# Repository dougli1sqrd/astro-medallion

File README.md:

# Astro Medallion

Electronics schematics, PCB layout, and software for the Astro Medallion.

The Astro Medallion is a 12 sided circuit board with LEDs that represent the astrological planets and their positions as a sort of clock. Earth is in the middle of 12 spokes of addressable RGB LEDs, where each spoke represents a sky position in the elliptical - each 30 degree section one of the zodiac signs. The distance along each spoke represents the distance away from the each planet is from the earth. Since it's geocentric planets may sometimes be closer or farther away from each other. Each planet will have a unique color.

There are Warm White LEDs along the edge of the PCB which represents the current field of view from your position on Earth - which rotates around the board once every 24 hours.

The project is a kind of translation of this page: https://ericofftherails.city/astrosim/

The LEDs are controlled by an esp32c3 microcontroller on a development board.

# Software

Fundamentally, the software controlling the board needs to:
1. Read the time in the RTC (Real Time Clock) chip on the PCB
2. Calculate Planetary positions
   1. Compute the positions of the planets relative to the earth based on the current time
   2. Compute the "facing" horizon position
3. Update the Display
   1. Send color data to the Addressable LEDs representing where each Planet is with respect to the zodiac sign
   2. Send white LED data representing the current horizon position
4. Sleep, and then awaken in time for the next update

Additionally, the software will have to be configurable mainly in setting the current time. Reading and Writing the current time will go over I2C to the RTC chip on board. This perhaps could be accomplished with a basic serial command line

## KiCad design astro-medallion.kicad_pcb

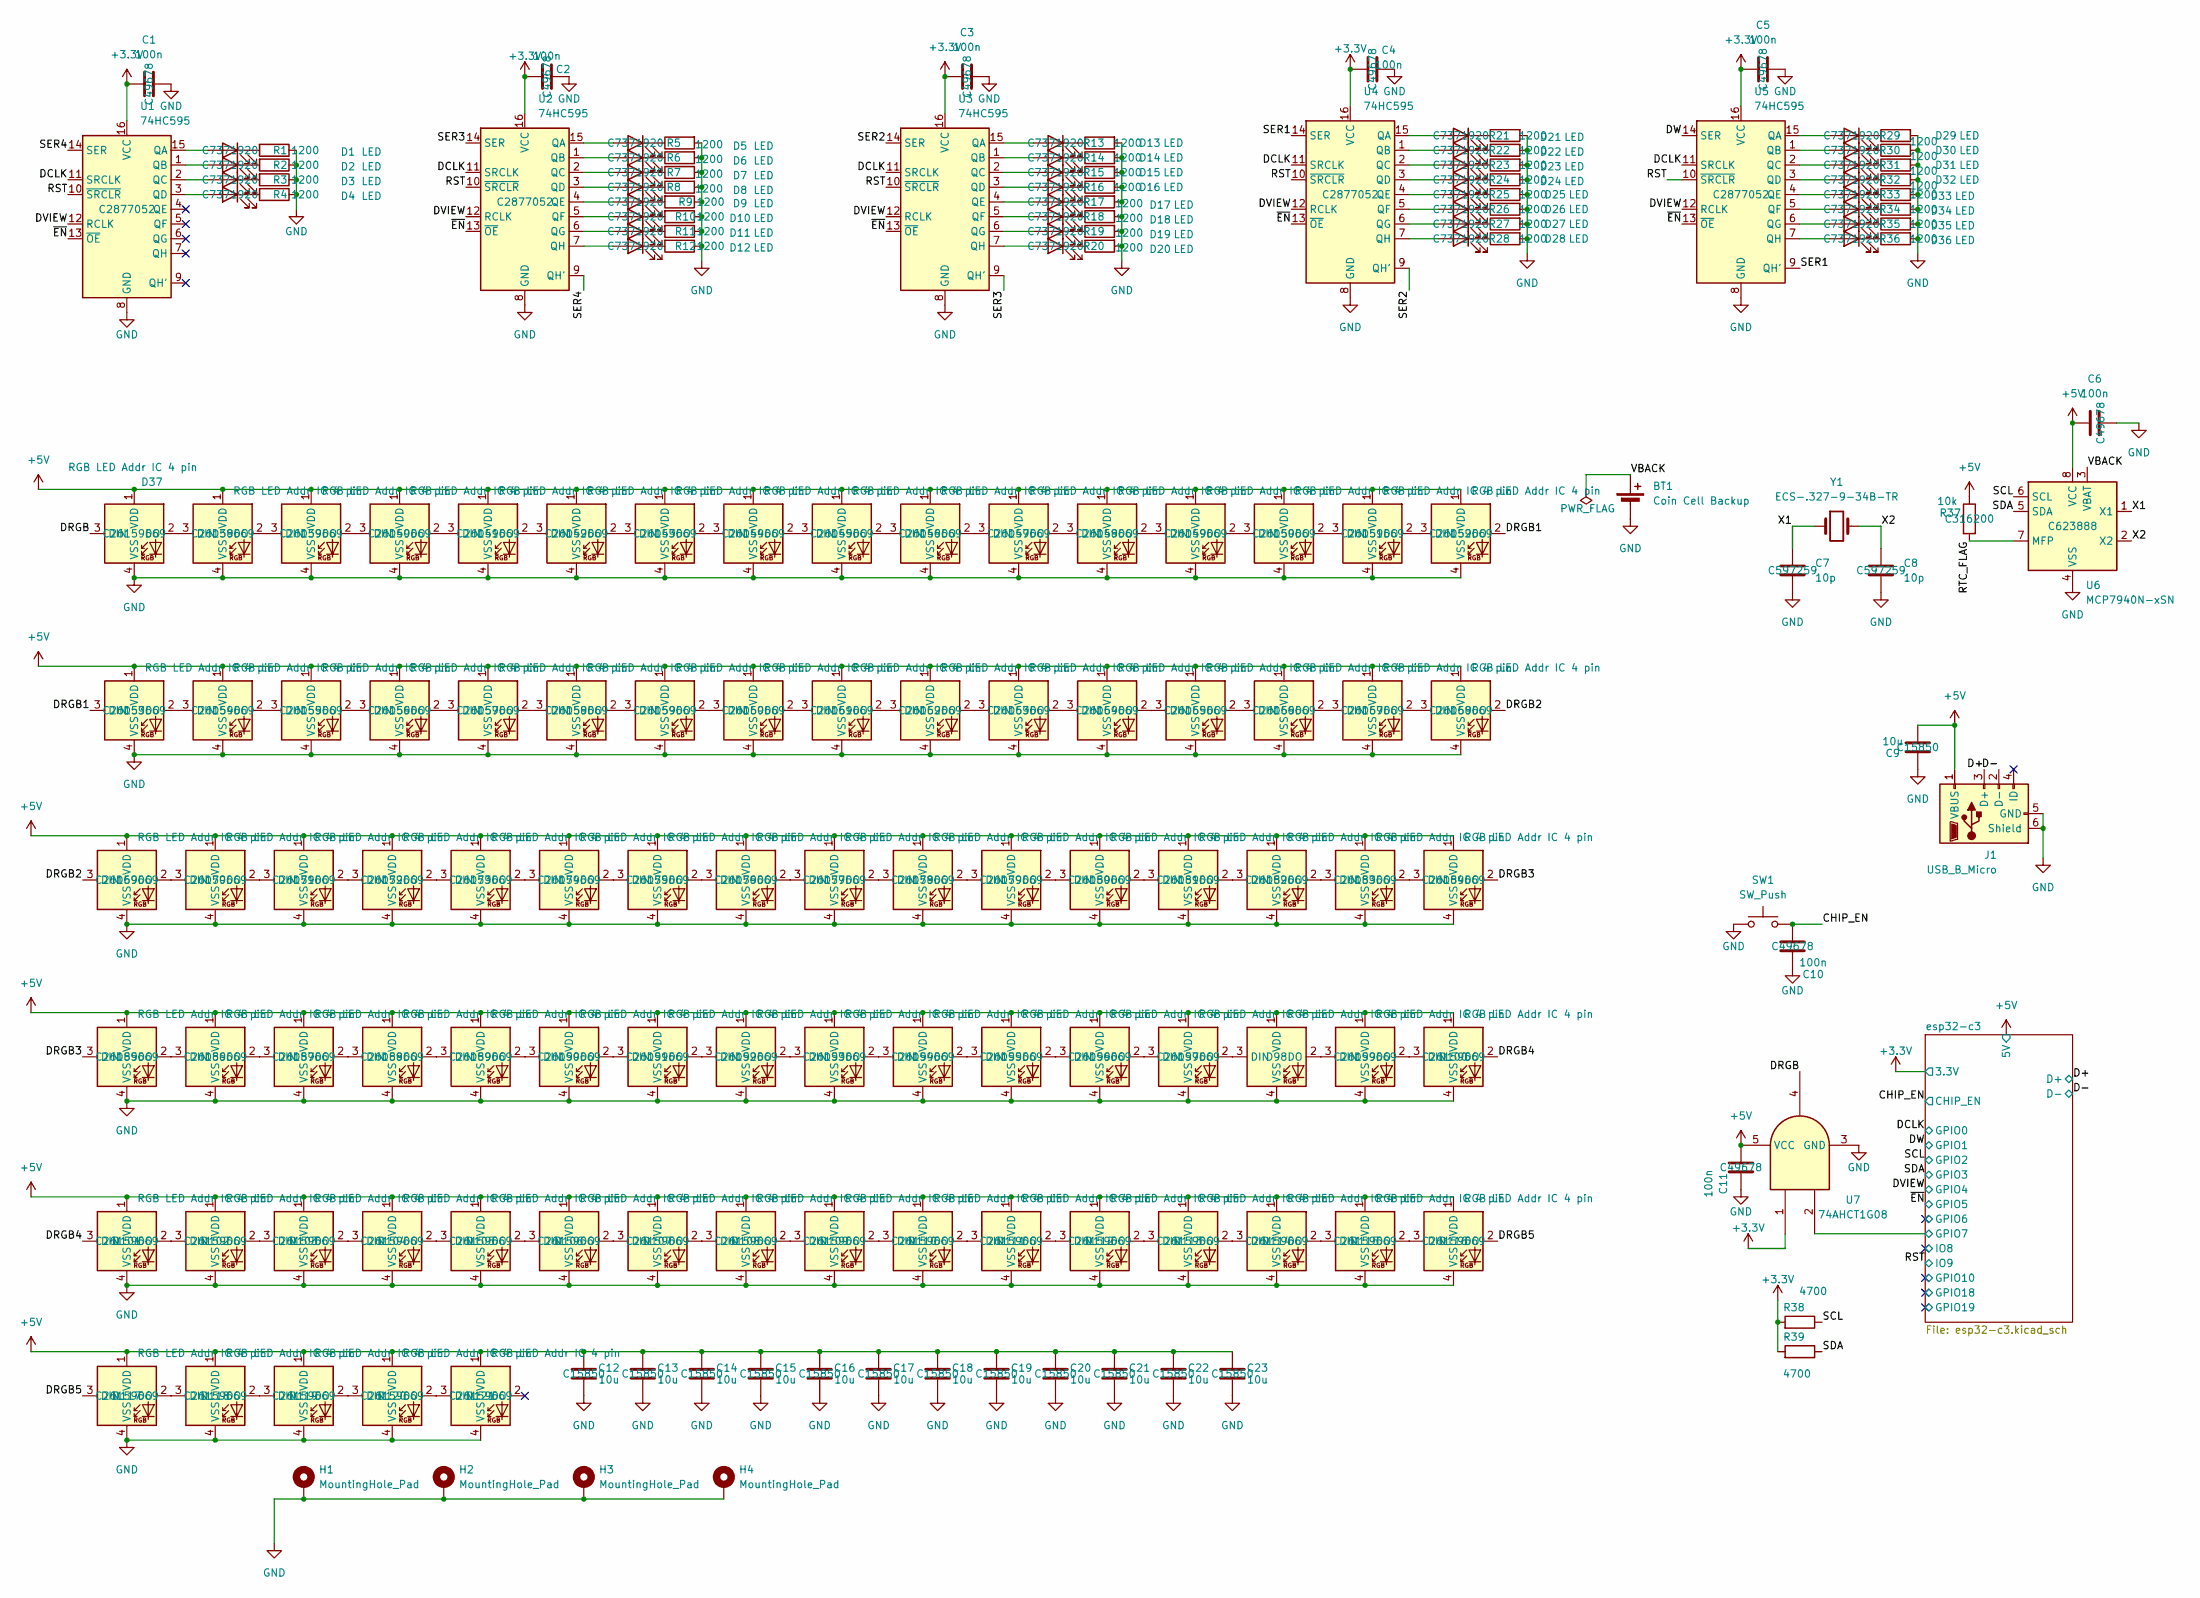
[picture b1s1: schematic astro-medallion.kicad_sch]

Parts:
BT1: Coin Cell Backup; BatteryHolder_Keystone_3002_1x2032
C1, C2, C3, C4, C5, C6, C10, C11: 100n; C_0805_2012Metric_Pad1.18x1.45mm_HandSolder; LCSC C49678
C7, C8: 10p; C_0805_2012Metric_Pad1.18x1.45mm_HandSolder; LCSC C597259
C9, C12, C13, C14, C15, C16, C17, C18, C19, C20, C21, C22, C23: 10u; C_0805_2012Metric_Pad1.18x1.45mm_HandSolder; LCSC C15850
D1, D2, D3, D4, D5, D6, D7, D8, D9, D10, D11, D12, D13, D14, D15, D16, D17, D18, D19, D20, D21, D22, D23, D24, D25, D26, D27, D28, D29, D30, D31, D32, D33, D34, D35, D36: LED; LED_PLCC_2835_Handsoldering; LCSC C7371920
D37, D38, D39, D40, D41, D42, D43, D44, D45, D46, D47, D48, D49, D50, D51, D52, D53, D54, D55, D56, D57, D58, D59, D60, D61, D62, D63, D64, D65, D66, D67, D68, D69, D70, D71, D72, D73, D74, D75, D76, D77, D78, D79, D80, D81, D82, D83, D84, D85, D86, D87, D88, D89, D90, D91, D92, D93, D94, D95, D96, D97, D98, D99, D100, D101, D102, D103, D104, D105, D106, D107, D108, D109, D110, D111, D112, D113, D114, D115, D116, D117, D118, D119, D120, D121: RGB LED Addr IC 4 pin; LED_PLCC3528_4P; LCSC C26159669
H1, H2, H3, H4: MountingHole_Pad; MountingHole_3.2mm_M3_Pad
J1: USB_B_Micro; USB_Micro-B_Molex-105133-0001; LCSC C586226
R1, R2, R3, R4, R5, R6, R7, R8, R9, R10, R11, R12, R13, R14, R15, R16, R17, R18, R19, R20, R21, R22, R23, R24, R25, R26, R27, R28, R29, R30, R31, R32, R33, R34, R35, R36: 1200; R_0805_2012Metric_Pad1.20x1.40mm_HandSolder
R37: 10k; R_0805_2012Metric_Pad1.20x1.40mm_HandSolder; LCSC C316200
R38, R39: 4700; R_0805_2012Metric_Pad1.20x1.40mm_HandSolder
SW1: SW_Push; SW_SPST_PTS645
U1, U2, U3, U4, U5: 74HC595; TSSOP-16_4.4x5mm_P0.65mm; LCSC C2877052
U6: MCP7940N-xSN; SOIC-8_3.9x4.9mm_P1.27mm; LCSC C623888
U7: 74AHCT1G08; SOT-23-5_HandSoldering; LCSC C460499
Y1: ECS-.327-9-34B-TR; Crystal_SMD_3215-2Pin_3.2x1.5mm; LCSC C2848222

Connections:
+3.3V: C1.1, C2.1, C3.1, C4.1, C5.1, R38.2, R39.2, U1.16 (VCC), U2.16 (VCC), U3.16 (VCC), U4.16 (VCC), U5.16 (VCC), U7.1; also elsewhere on the board
+5V: C6.1, C9.1, C11.1, C12.2, C13.2, C14.2, C15.2, C16.2, C17.2, C18.2, C19.2, C20.2, C21.2, C22.2, C23.2, D37.1 (VDD), D38.1 (VDD), D39.1 (VDD), D40.1 (VDD), D41.1 (VDD), D42.1 (VDD), D43.1 (VDD), D44.1 (VDD), D45.1 (VDD), D46.1 (VDD), D47.1 (VDD), D48.1 (VDD), D49.1 (VDD), D50.1 (VDD), D51.1 (VDD), D52.1 (VDD), D53.1 (VDD), D54.1 (VDD), D55.1 (VDD), D56.1 (VDD), D57.1 (VDD), D58.1 (VDD), D59.1 (VDD), D60.1 (VDD), D61.1 (VDD), D62.1 (VDD), D63.1 (VDD), D64.1 (VDD), D65.1 (VDD), D66.1 (VDD), D67.1 (VDD), D68.1 (VDD), D69.1 (VDD), D70.1 (VDD), D71.1 (VDD), D72.1 (VDD), D73.1 (VDD), D74.1 (VDD), D75.1 (VDD), D76.1 (VDD), D77.1 (VDD), D78.1 (VDD), D79.1 (VDD), D80.1 (VDD), D81.1 (VDD), D82.1 (VDD), D83.1 (VDD), D84.1 (VDD), D85.1 (VDD), D86.1 (VDD), D87.1 (VDD), D88.1 (VDD), D89.1 (VDD), D90.1 (VDD), D91.1 (VDD), D92.1 (VDD), D93.1 (VDD), D94.1 (VDD), D95.1 (VDD), D96.1 (VDD), D97.1 (VDD), D98.1 (VDD), D99.1 (VDD), D100.1 (VDD), D101.1 (VDD), D102.1 (VDD), D103.1 (VDD), D104.1 (VDD), D105.1 (VDD), D106.1 (VDD), D107.1 (VDD), D108.1 (VDD), D109.1 (VDD), D110.1 (VDD), D111.1 (VDD), D112.1 (VDD), D113.1 (VDD), D114.1 (VDD), D115.1 (VDD), D116.1 (VDD), D117.1 (VDD), D118.1 (VDD), D119.1 (VDD), D120.1 (VDD), D121.1 (VDD), J1.1 (VBUS), R37.1, U6.8 (VCC), U7.5 (VCC); also elsewhere on the board
/CHIP_EN: C10.2, SW1.2; also elsewhere on the board
/D+: J1.3 (D+); also elsewhere on the board
/D-: J1.2 (D-); also elsewhere on the board
/DCLK: U1.11 (SRCLK), U2.11 (SRCLK), U3.11 (SRCLK), U4.11 (SRCLK), U5.11 (SRCLK); also elsewhere on the board
/DRGB: D37.3 (DIN), U7.4
/DRGB1: D52.2 (DO), D53.3 (DIN)
/DRGB2: D68.2 (DO), D69.3 (DIN)
/DRGB3: D84.2 (DO), D85.3 (DIN)
/DRGB4: D100.2 (DO), D101.3 (DIN)
/DRGB5: D116.2 (DO), D117.3 (DIN)
/DVIEW: U1.12 (RCLK), U2.12 (RCLK), U3.12 (RCLK), U4.12 (RCLK), U5.12 (RCLK); also elsewhere on the board
/DW: U5.14 (SER); also elsewhere on the board
/RST: U1.10 (~SRCLR), U2.10 (~SRCLR), U3.10 (~SRCLR), U4.10 (~SRCLR), U5.10 (~SRCLR); also elsewhere on the board
/RTC_FLAG: R37.2, U6.7 (MFP)
/SCL: R38.1, U6.6 (SCL); also elsewhere on the board
/SDA: R39.1, U6.5 (SDA); also elsewhere on the board
/SER1: U4.14 (SER), U5.9 (QH')
/SER2: U3.14 (SER), U4.9 (QH')
/SER3: U2.14 (SER), U3.9 (QH')
/SER4: U1.14 (SER), U2.9 (QH')
/VBACK: BT1.1 (+), U6.3 (VBAT)
/X1: C7.1, U6.1 (X1), Y1.1
/X2: C8.1, U6.2 (X2), Y1.2
/esp32-c3/GPIO7: U7.2; also elsewhere on the board
/~EN: U1.13 (~OE), U2.13 (~OE), U3.13 (~OE), U4.13 (~OE), U5.13 (~OE); also elsewhere on the board
GND: BT1.2 (-), C1.2, C2.2, C3.2, C4.2, C5.2, C6.2, C7.2, C8.2, C9.2, C10.1, C11.2, C12.1, C13.1, C14.1, C15.1, C16.1, C17.1, C18.1, C19.1, C20.1, C21.1, C22.1, C23.1, D37.4 (VSS), D38.4 (VSS), D39.4 (VSS), D40.4 (VSS), D41.4 (VSS), D42.4 (VSS), D43.4 (VSS), D44.4 (VSS), D45.4 (VSS), D46.4 (VSS), D47.4 (VSS), D48.4 (VSS), D49.4 (VSS), D50.4 (VSS), D51.4 (VSS), D52.4 (VSS), D53.4 (VSS), D54.4 (VSS), D55.4 (VSS), D56.4 (VSS), D57.4 (VSS), D58.4 (VSS), D59.4 (VSS), D60.4 (VSS), D61.4 (VSS), D62.4 (VSS), D63.4 (VSS), D64.4 (VSS), D65.4 (VSS), D66.4 (VSS), D67.4 (VSS), D68.4 (VSS), D69.4 (VSS), D70.4 (VSS), D71.4 (VSS), D72.4 (VSS), D73.4 (VSS), D74.4 (VSS), D75.4 (VSS), D76.4 (VSS), D77.4 (VSS), D78.4 (VSS), D79.4 (VSS), D80.4 (VSS), D81.4 (VSS), D82.4 (VSS), D83.4 (VSS), D84.4 (VSS), D85.4 (VSS), D86.4 (VSS), D87.4 (VSS), D88.4 (VSS), D89.4 (VSS), D90.4 (VSS), D91.4 (VSS), D92.4 (VSS), D93.4 (VSS), D94.4 (VSS), D95.4 (VSS), D96.4 (VSS), D97.4 (VSS), D98.4 (VSS), D99.4 (VSS), D100.4 (VSS), D101.4 (VSS), D102.4 (VSS), D103.4 (VSS), D104.4 (VSS), D105.4 (VSS), D106.4 (VSS), D107.4 (VSS), D108.4 (VSS), D109.4 (VSS), D110.4 (VSS), D111.4 (VSS), D112.4 (VSS), D113.4 (VSS), D114.4 (VSS), D115.4 (VSS), D116.4 (VSS), D117.4 (VSS), D118.4 (VSS), D119.4 (VSS), D120.4 (VSS), D121.4 (VSS), H1.1, H2.1, H3.1, H4.1, J1.5 (GND), J1.6 (Shield), R1.1, R2.1, R3.1, R4.1, R5.2, R6.2, R7.2, R8.2, R9.1, R10.1, R11.1, R12.1, R13.2, R14.2, R15.2, R16.2, R17.2, R18.2, R19.2, R20.2, R21.2, R22.2, R23.2, R24.2, R25.2, R26.2, R27.2, R28.2, R29.2, R30.2, R31.2, R32.2, R33.2, R34.2, R35.2, R36.2, SW1.1, U1.8 (GND), U2.8 (GND), U3.8 (GND), U4.8 (GND), U5.8 (GND), U6.4 (VSS), U7.3 (GND); also elsewhere on the board
unnamed: D1.2 (A), U1.15 (QA)
unnamed: D1.1 (K), R1.2
unnamed: D2.2 (A), U1.1 (QB)
unnamed: D2.1 (K), R2.2
unnamed: D3.2 (A), U1.2 (QC)
unnamed: D3.1 (K), R3.2
unnamed: D4.2 (A), U1.3 (QD)
unnamed: D4.1 (K), R4.2
unnamed: D5.2 (A), U2.15 (QA)
unnamed: D5.1 (K), R5.1
unnamed: D6.2 (A), U2.1 (QB)
unnamed: D6.1 (K), R6.1
unnamed: D7.2 (A), U2.2 (QC)
unnamed: D7.1 (K), R7.1
unnamed: D8.2 (A), U2.3 (QD)
unnamed: D8.1 (K), R8.1
unnamed: D9.2 (A), U2.4 (QE)
unnamed: D9.1 (K), R9.2
unnamed: D10.2 (A), U2.5 (QF)
unnamed: D10.1 (K), R10.2
unnamed: D11.2 (A), U2.6 (QG)
unnamed: D11.1 (K), R11.2
unnamed: D12.2 (A), U2.7 (QH)
unnamed: D12.1 (K), R12.2
unnamed: D13.2 (A), U3.15 (QA)
unnamed: D13.1 (K), R13.1
unnamed: D14.2 (A), U3.1 (QB)
unnamed: D14.1 (K), R14.1
unnamed: D15.2 (A), U3.2 (QC)
unnamed: D15.1 (K), R15.1
unnamed: D16.2 (A), U3.3 (QD)
unnamed: D16.1 (K), R16.1
unnamed: D17.2 (A), U3.4 (QE)
unnamed: D17.1 (K), R17.1
unnamed: D18.2 (A), U3.5 (QF)
unnamed: D18.1 (K), R18.1
unnamed: D19.2 (A), U3.6 (QG)
unnamed: D19.1 (K), R19.1
unnamed: D20.2 (A), U3.7 (QH)
unnamed: D20.1 (K), R20.1
unnamed: D21.2 (A), U4.15 (QA)
unnamed: D21.1 (K), R21.1
unnamed: D22.2 (A), U4.1 (QB)
unnamed: D22.1 (K), R22.1
unnamed: D23.2 (A), U4.2 (QC)
unnamed: D23.1 (K), R23.1
unnamed: D24.2 (A), U4.3 (QD)
unnamed: D24.1 (K), R24.1
unnamed: D25.2 (A), U4.4 (QE)
unnamed: D25.1 (K), R25.1
unnamed: D26.2 (A), U4.5 (QF)
unnamed: D26.1 (K), R26.1
unnamed: D27.2 (A), U4.6 (QG)
unnamed: D27.1 (K), R27.1
unnamed: D28.2 (A), U4.7 (QH)
unnamed: D28.1 (K), R28.1
unnamed: D29.2 (A), U5.15 (QA)
unnamed: D29.1 (K), R29.1
unnamed: D30.2 (A), U5.1 (QB)
unnamed: D30.1 (K), R30.1
unnamed: D31.2 (A), U5.2 (QC)
unnamed: D31.1 (K), R31.1
unnamed: D32.2 (A), U5.3 (QD)
unnamed: D32.1 (K), R32.1
unnamed: D33.2 (A), U5.4 (QE)
unnamed: D33.1 (K), R33.1
unnamed: D34.2 (A), U5.5 (QF)
unnamed: D34.1 (K), R34.1
unnamed: D35.2 (A), U5.6 (QG)
unnamed: D35.1 (K), R35.1
unnamed: D36.2 (A), U5.7 (QH)
unnamed: D36.1 (K), R36.1
unnamed: D37.2 (DO), D38.3 (DIN)
unnamed: D38.2 (DO), D39.3 (DIN)
unnamed: D39.2 (DO), D40.3 (DIN)
unnamed: D40.2 (DO), D41.3 (DIN)
unnamed: D41.2 (DO), D42.3 (DIN)
unnamed: D42.2 (DO), D43.3 (DIN)
unnamed: D43.2 (DO), D44.3 (DIN)
unnamed: D44.2 (DO), D45.3 (DIN)
unnamed: D45.2 (DO), D46.3 (DIN)
unnamed: D46.2 (DO), D47.3 (DIN)
unnamed: D47.2 (DO), D48.3 (DIN)
unnamed: D48.2 (DO), D49.3 (DIN)
unnamed: D49.2 (DO), D50.3 (DIN)
unnamed: D50.2 (DO), D51.3 (DIN)
unnamed: D51.2 (DO), D52.3 (DIN)
unnamed: D53.2 (DO), D54.3 (DIN)
unnamed: D54.2 (DO), D55.3 (DIN)
unnamed: D55.2 (DO), D56.3 (DIN)
unnamed: D56.2 (DO), D57.3 (DIN)
unnamed: D57.2 (DO), D58.3 (DIN)
unnamed: D58.2 (DO), D59.3 (DIN)
unnamed: D59.2 (DO), D60.3 (DIN)
unnamed: D60.2 (DO), D61.3 (DIN)
unnamed: D61.2 (DO), D62.3 (DIN)
unnamed: D62.2 (DO), D63.3 (DIN)
unnamed: D63.2 (DO), D64.3 (DIN)
unnamed: D64.2 (DO), D65.3 (DIN)
unnamed: D65.2 (DO), D66.3 (DIN)
unnamed: D66.2 (DO), D67.3 (DIN)
unnamed: D67.2 (DO), D68.3 (DIN)
unnamed: D69.2 (DO), D70.3 (DIN)
unnamed: D70.2 (DO), D71.3 (DIN)
unnamed: D71.2 (DO), D72.3 (DIN)
unnamed: D72.2 (DO), D73.3 (DIN)
unnamed: D73.2 (DO), D74.3 (DIN)
unnamed: D74.2 (DO), D75.3 (DIN)
unnamed: D75.2 (DO), D76.3 (DIN)
unnamed: D76.2 (DO), D77.3 (DIN)
unnamed: D77.2 (DO), D78.3 (DIN)
unnamed: D78.2 (DO), D79.3 (DIN)
unnamed: D79.2 (DO), D80.3 (DIN)
unnamed: D80.2 (DO), D81.3 (DIN)
unnamed: D81.2 (DO), D82.3 (DIN)
unnamed: D82.2 (DO), D83.3 (DIN)
unnamed: D83.2 (DO), D84.3 (DIN)
unnamed: D85.2 (DO), D86.3 (DIN)
unnamed: D86.2 (DO), D87.3 (DIN)
unnamed: D87.2 (DO), D88.3 (DIN)
unnamed: D88.2 (DO), D89.3 (DIN)
unnamed: D89.2 (DO), D90.3 (DIN)
unnamed: D90.2 (DO), D91.3 (DIN)
unnamed: D91.2 (DO), D92.3 (DIN)
unnamed: D92.2 (DO), D93.3 (DIN)
unnamed: D93.2 (DO), D94.3 (DIN)
unnamed: D94.2 (DO), D95.3 (DIN)
unnamed: D95.2 (DO), D96.3 (DIN)
unnamed: D96.2 (DO), D97.3 (DIN)
unnamed: D97.2 (DO), D98.3 (DIN)
unnamed: D98.2 (DO), D99.3 (DIN)
unnamed: D99.2 (DO), D100.3 (DIN)
unnamed: D101.2 (DO), D102.3 (DIN)
unnamed: D102.2 (DO), D103.3 (DIN)
unnamed: D103.2 (DO), D104.3 (DIN)
unnamed: D104.2 (DO), D105.3 (DIN)
unnamed: D105.2 (DO), D106.3 (DIN)
unnamed: D106.2 (DO), D107.3 (DIN)
unnamed: D107.2 (DO), D108.3 (DIN)
unnamed: D108.2 (DO), D109.3 (DIN)
unnamed: D109.2 (DO), D110.3 (DIN)
unnamed: D110.2 (DO), D111.3 (DIN)
unnamed: D111.2 (DO), D112.3 (DIN)
unnamed: D112.2 (DO), D113.3 (DIN)
unnamed: D113.2 (DO), D114.3 (DIN)
unnamed: D114.2 (DO), D115.3 (DIN)
unnamed: D115.2 (DO), D116.3 (DIN)
unnamed: D117.2 (DO), D118.3 (DIN)
unnamed: D118.2 (DO), D119.3 (DIN)
unnamed: D119.2 (DO), D120.3 (DIN)
unnamed: D120.2 (DO), D121.3 (DIN)

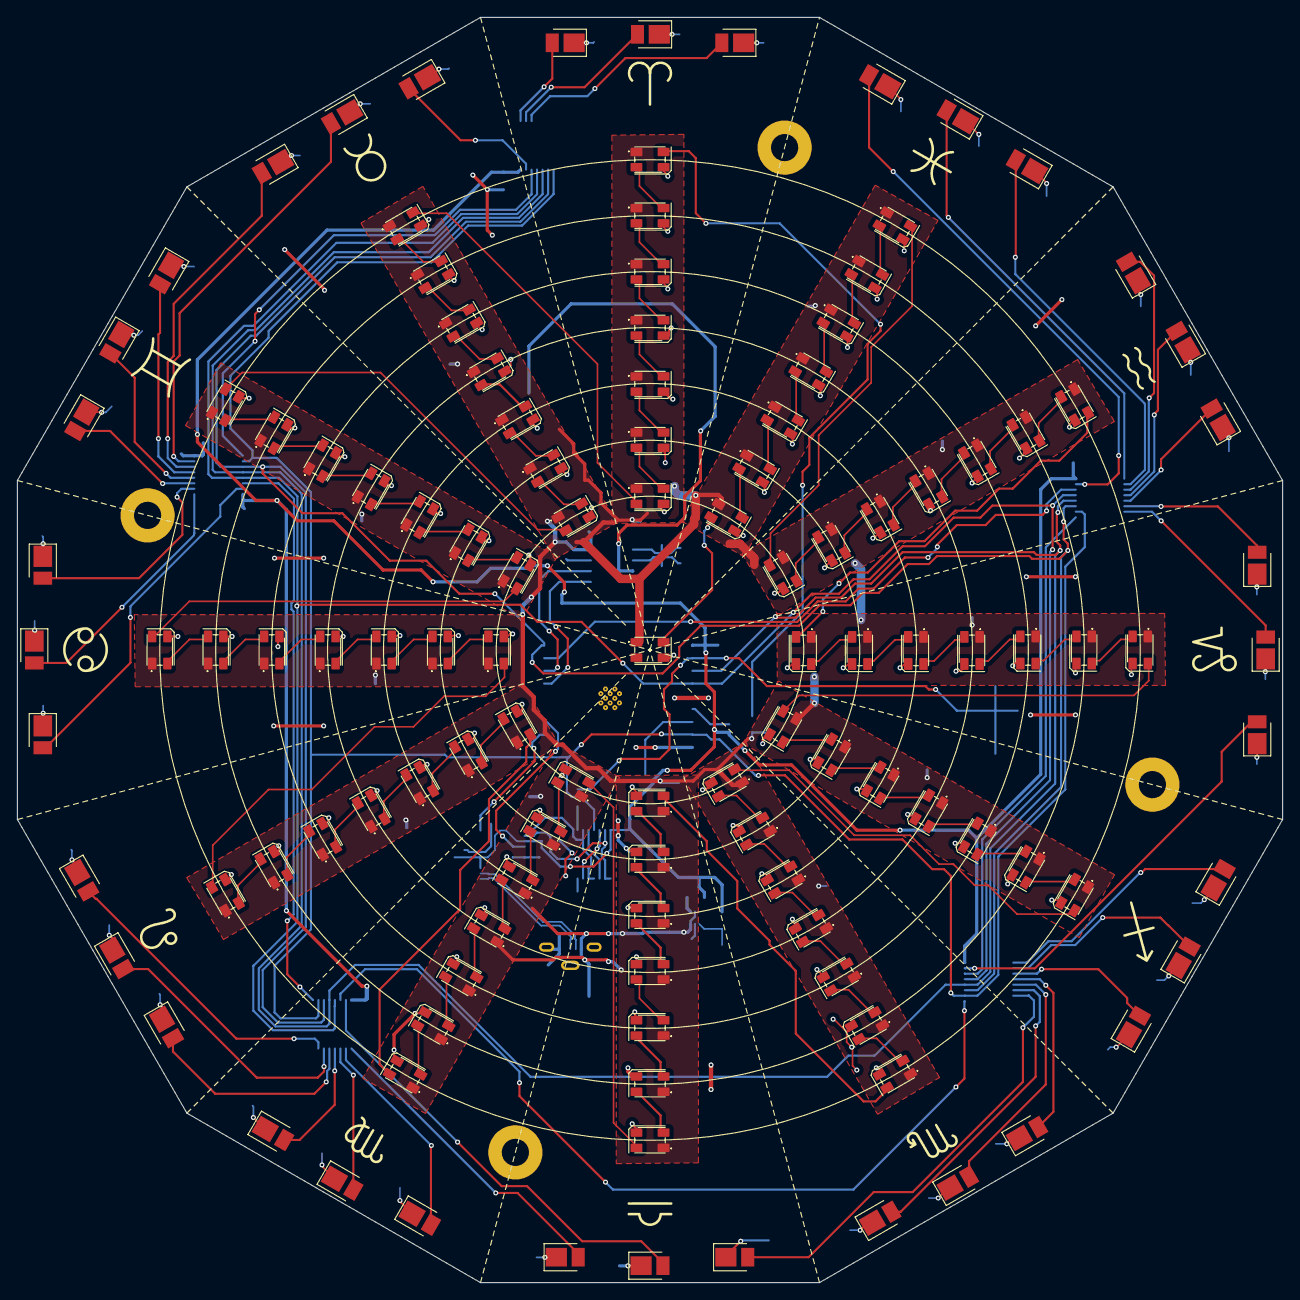
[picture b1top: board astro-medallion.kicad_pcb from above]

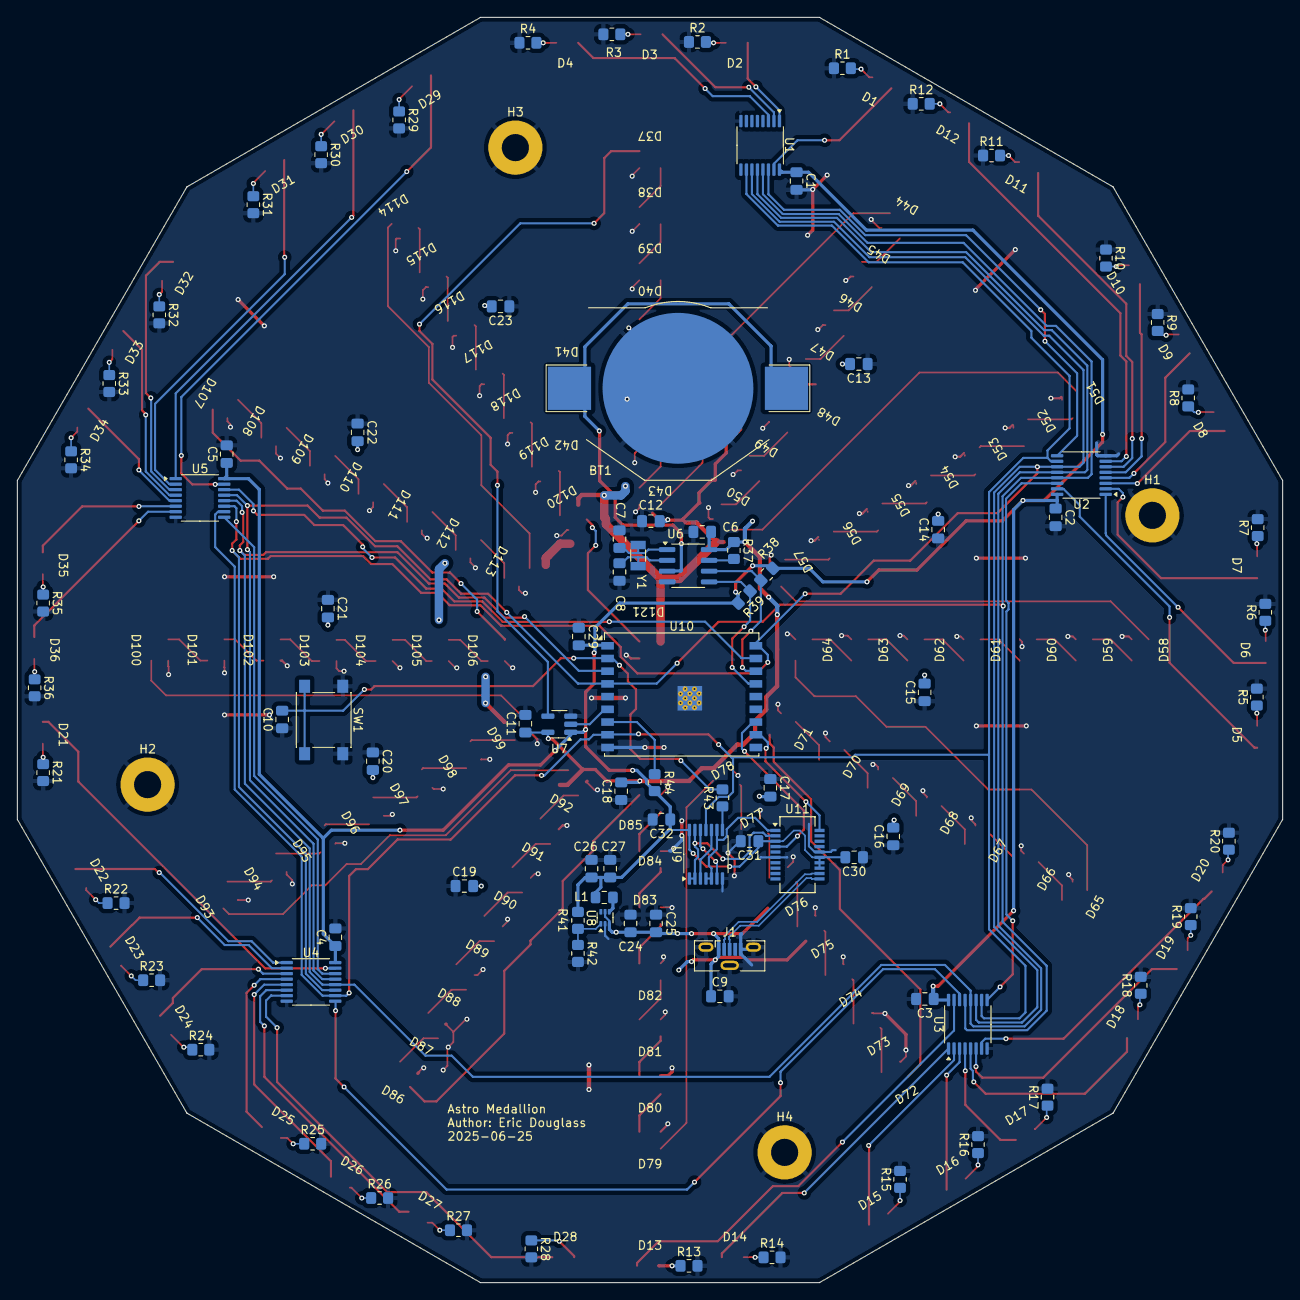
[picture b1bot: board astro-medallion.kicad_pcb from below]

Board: 2 copper layers, 149.3 x 149.3 mm, 215 parts (90 on the bottom side), 189 nets.

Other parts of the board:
C24, C26, C27: 10u; C_0805_2012Metric_Pad1.18x1.45mm_HandSolder
C25, C29, C30, C31, C32: 100n; C_0805_2012Metric_Pad1.18x1.45mm_HandSolder
L1: 1u; L_0805_2012Metric_Pad1.15x1.40mm_HandSolder
R41: 680k; R_0805_2012Metric_Pad1.20x1.40mm_HandSolder
R42: 150k; R_0805_2012Metric_Pad1.20x1.40mm_HandSolder
R43, R44: 10k; R_0805_2012Metric_Pad1.20x1.40mm_HandSolder
U8: TLV62569ADRL; SOT-563
U9: 74HC00; TSSOP-14_4.4x5mm_P0.65mm
U10: ESP32-C3-WROOM-02U
U11: FT231XS; SSOP-20_3.9x8.7mm_P0.635mm

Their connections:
+3.3V: C26.1, C27.1, C29.2, C30.2, C31.1, C32.1, L1.2, R41.1, R44.2, U9.14 (VCC), U10.1 (3V3), U11.3 (VCCIO), U11.13 (3V3OUT), U11.14 (~RESET), U11.15 (VCC); also elsewhere on the board
+5V: C24.1, C25.1, U8.3 (VIN), U8.5 (EN); also elsewhere on the board
/CHIP_EN: R43.2, U10.2 (EN); also elsewhere on the board
/D+: U11.11 (USBDP); also elsewhere on the board
/D-: U11.12 (USBDM); also elsewhere on the board
/DCLK: U10.18 (IO0); also elsewhere on the board
/DVIEW: U10.3 (IO4); also elsewhere on the board
/DW: U10.17 (IO1); also elsewhere on the board
/RST: U9.11, U10.8 (IO9); also elsewhere on the board
/SCL: U10.16 (IO2); also elsewhere on the board
/SDA: U10.15 (IO3); also elsewhere on the board
/esp32-c3/DTR: U9.4, U9.5, U9.9, U11.1 (~DTR)
/esp32-c3/GPIO7: U10.6 (IO7); also elsewhere on the board
/esp32-c3/IO8: R44.1, U10.7 (IO8)
/esp32-c3/RTS: U9.1, U9.2, U9.13, U11.2 (~RTS)
/esp32-c3/RX: U10.11 (IO20/RXD), U11.20 (TXD)
/esp32-c3/TX: U10.12 (IO21/TXD), U11.4 (RXD)
/~EN: U10.4 (IO5); also elsewhere on the board
GND: C24.2, C25.2, C26.2, C27.2, C29.1, C30.1, C31.2, C32.2, R42.2, U8.2 (GND), U9.7 (GND), U10.9 (GND), U10.19 (GND), U11.6 (GND), U11.16 (GND); also elsewhere on the board
unnamed: R43.1, U9.8
unnamed: R41.2, R42.1, U8.1 (FB)
unnamed: L1.1, U8.4 (SW)
unnamed: U9.3, U9.10
unnamed: U9.6, U9.12

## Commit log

2025-01-23 initial commmit of astro-medallion. Kicad project and controller code
2025-01-23 cleaning up files and removing some unused code
2025-01-23 reversed the labels of the signs to increase counter-clockwise
2026-01-17 committing everything that's part of the current production of astro medallion
